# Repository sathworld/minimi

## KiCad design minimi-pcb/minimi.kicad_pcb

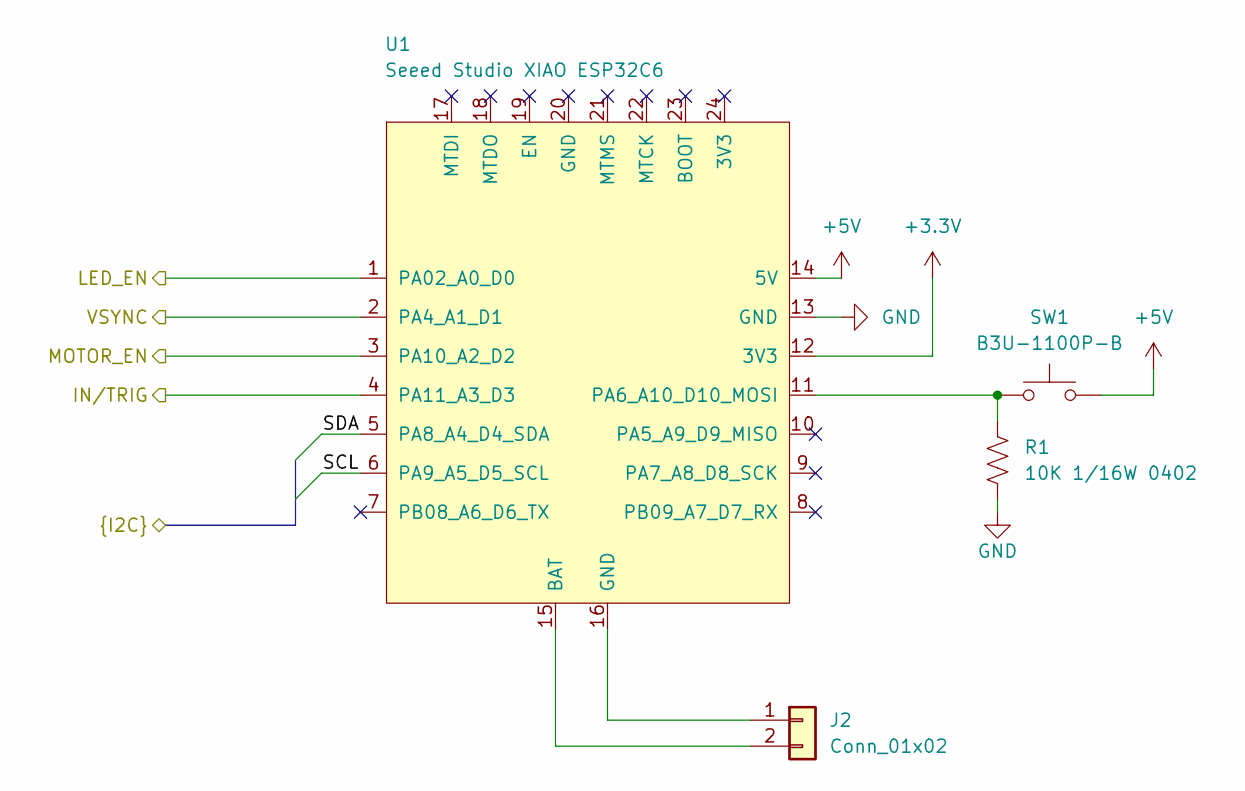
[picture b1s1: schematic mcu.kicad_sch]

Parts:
J2: Conn_01x02; TestPoint_2Pads_Pitch2.54mm_Drill0.8mm
R1: 10K 1/16W 0402; R_0402_1005Metric
SW1: B3U-1100P-B; B3U1100PB
U1: Seeed Studio XIAO ESP32C6; XIAO-ESP32-C6-SMD

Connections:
+3.3V: U1.12 (3V3)
+5V: SW1.2, U1.14 (5V); also elsewhere on the board
/HB-MOTOR-BLOCK/IN/TRIG: U1.3 (PA10_A2_D2); also elsewhere on the board
/HB-MOTOR-BLOCK/MOTOR_EN: U1.4 (PA11_A3_D3); also elsewhere on the board
/HB-MOTOR-BLOCK/SCL: U1.6 (PA9_A5_D5_SCL); also elsewhere on the board
/HB-MOTOR-BLOCK/SDA: U1.5 (PA8_A4_D4_SDA); also elsewhere on the board
/LED-BLOCK/LED_EN: U1.1 (PA02_A0_D0); also elsewhere on the board
/LED-BLOCK/VSYNC: U1.2 (PA4_A1_D1); also elsewhere on the board
GND: R1.2, U1.13 (GND); also elsewhere on the board
unnamed: J2.1, U1.16 (GND)
unnamed: J2.2, U1.15 (BAT)
unnamed: R1.1, SW1.1, U1.11 (PA6_A10_D10_MOSI)

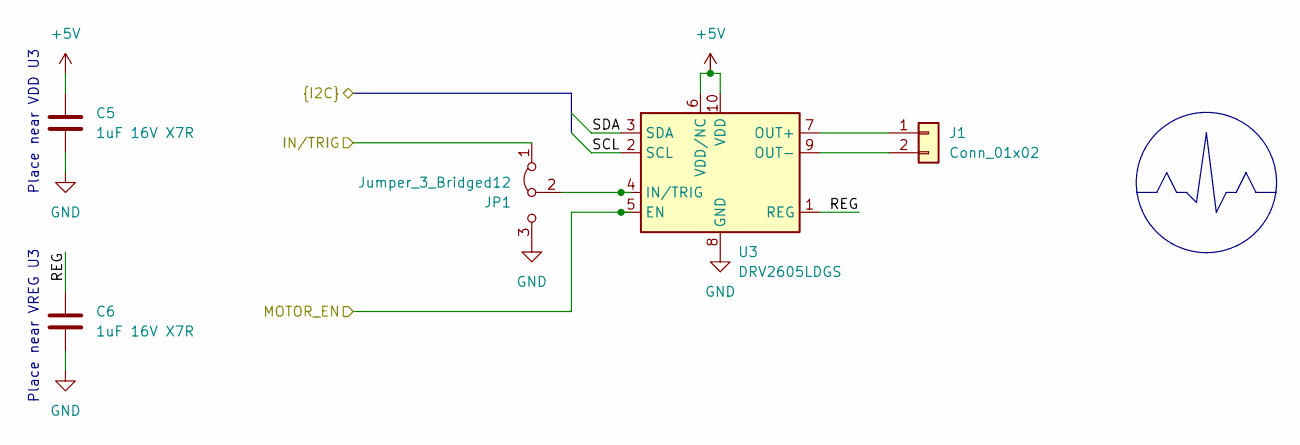
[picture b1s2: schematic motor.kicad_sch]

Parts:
C5, C6: 1uF 16V X7R; C_0603_1608Metric
J1: Conn_01x02; TestPoint_2Pads_Pitch2.54mm_Drill0.8mm
JP1: Jumper_3_Bridged12; SolderJumper-3_P1.3mm_Bridged12_RoundedPad1.0x1.5mm
U3: DRV2605LDGS; VSSOP-10_3x3mm_P0.5mm

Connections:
+5V: C5.1, U3.6 (VDD/NC), U3.10 (VDD); also elsewhere on the board
/HB-MOTOR-BLOCK/IN/TRIG: JP1.1 (A); also elsewhere on the board
/HB-MOTOR-BLOCK/MOTOR_EN: U3.5 (EN); also elsewhere on the board
/HB-MOTOR-BLOCK/REG: C6.1, U3.1 (REG)
/HB-MOTOR-BLOCK/SCL: U3.2 (SCL); also elsewhere on the board
/HB-MOTOR-BLOCK/SDA: U3.3 (SDA); also elsewhere on the board
GND: C5.2, C6.2, JP1.3 (B), U3.8 (GND); also elsewhere on the board
unnamed: J1.1, U3.7 (OUT+)
unnamed: J1.2, U3.9 (OUT-)
unnamed: JP1.2 (C), U3.4 (IN/TRIG)

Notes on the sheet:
Place near VREG U3
Place near VDD U3

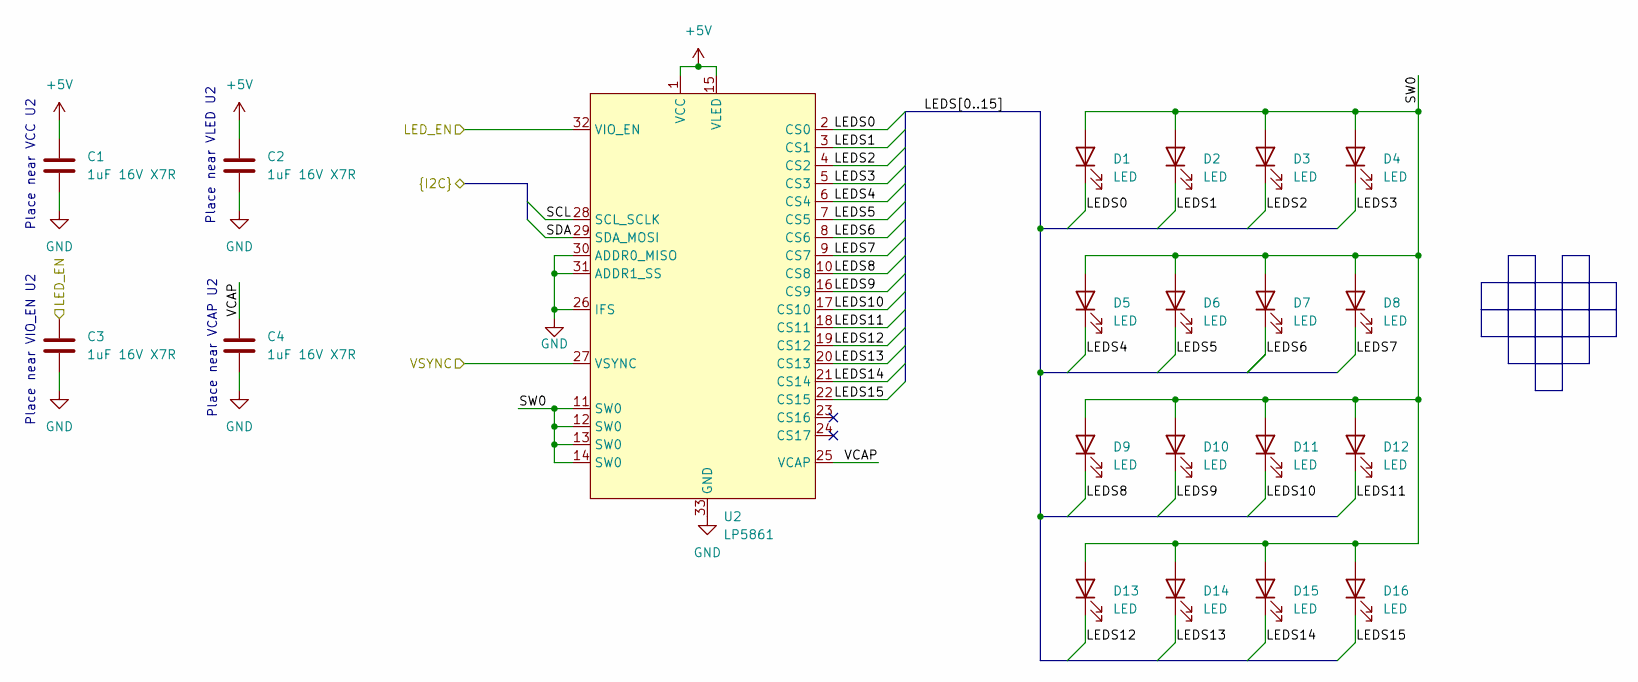
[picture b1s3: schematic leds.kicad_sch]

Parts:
C1, C2, C3, C4: 1uF 16V X7R; C_0603_1608Metric
D1, D2, D3, D4, D5, D6, D7, D8, D9, D10, D11, D12, D13, D14, D15, D16: LED; LED_0603_1608Metric
U2: LP5861; VQFN-32-1EP_4x4mm_P0.4mm_EP2.8x2.8mm_ThermalVias

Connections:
+5V: C1.1, C2.1, U2.1 (VCC), U2.15 (VLED); also elsewhere on the board
/HB-MOTOR-BLOCK/SCL: U2.28 (SCL_SCLK); also elsewhere on the board
/HB-MOTOR-BLOCK/SDA: U2.29 (SDA_MOSI); also elsewhere on the board
/LED-BLOCK/LEDS0: D1.1 (K), U2.2 (CS0)
/LED-BLOCK/LEDS1: D2.1 (K), U2.3 (CS1)
/LED-BLOCK/LEDS2: D3.1 (K), U2.4 (CS2)
/LED-BLOCK/LEDS3: D4.1 (K), U2.5 (CS3)
/LED-BLOCK/LEDS4: D5.1 (K), U2.6 (CS4)
/LED-BLOCK/LEDS5: D6.1 (K), U2.7 (CS5)
/LED-BLOCK/LEDS6: D7.1 (K), U2.8 (CS6)
/LED-BLOCK/LEDS7: D8.1 (K), U2.9 (CS7)
/LED-BLOCK/LEDS8: D9.1 (K), U2.10 (CS8)
/LED-BLOCK/LEDS9: D10.1 (K), U2.16 (CS9)
/LED-BLOCK/LEDS10: D11.1 (K), U2.17 (CS10)
/LED-BLOCK/LEDS11: D12.1 (K), U2.18 (CS11)
/LED-BLOCK/LEDS12: D13.1 (K), U2.19 (CS12)
/LED-BLOCK/LEDS13: D14.1 (K), U2.20 (CS13)
/LED-BLOCK/LEDS14: D15.1 (K), U2.21 (CS14)
/LED-BLOCK/LEDS15: D16.1 (K), U2.22 (CS15)
/LED-BLOCK/LED_EN: C3.1, U2.32 (VIO_EN); also elsewhere on the board
/LED-BLOCK/SW0: D1.2 (A), D2.2 (A), D3.2 (A), D4.2 (A), D5.2 (A), D6.2 (A), D7.2 (A), D8.2 (A), D9.2 (A), D10.2 (A), D11.2 (A), D12.2 (A), D13.2 (A), D14.2 (A), D15.2 (A), D16.2 (A), U2.11 (SW0), U2.12 (SW0), U2.13 (SW0), U2.14 (SW0)
/LED-BLOCK/VCAP: C4.1, U2.25 (VCAP)
/LED-BLOCK/VSYNC: U2.27 (VSYNC); also elsewhere on the board
GND: C1.2, C2.2, C3.2, C4.2, U2.26 (IFS), U2.30 (ADDR0_MISO), U2.31 (ADDR1_SS), U2.33 (GND); also elsewhere on the board

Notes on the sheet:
Place near VCC U2
Place near VCAP U2
Place near VLED U2
Place near VIO_EN U2

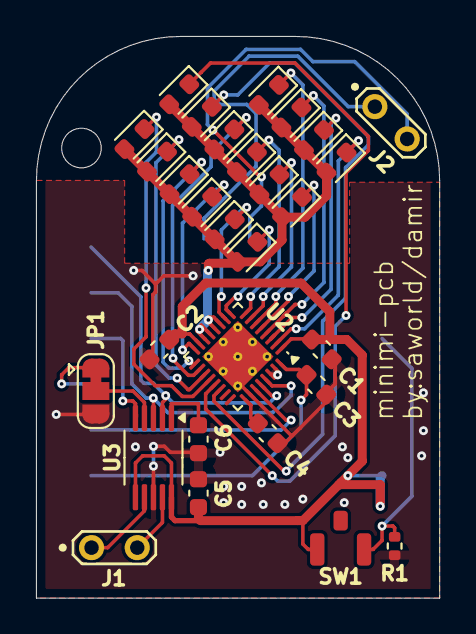
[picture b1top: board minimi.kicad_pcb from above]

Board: 2 copper layers, 22.4 x 31.2 mm, 30 parts (1 on the bottom side), 33 nets.

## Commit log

2024-10-29 Added the pcb to the repo Signed-off-by: Damir Gazizullin <dgazizul@uwaterloo.ca>
